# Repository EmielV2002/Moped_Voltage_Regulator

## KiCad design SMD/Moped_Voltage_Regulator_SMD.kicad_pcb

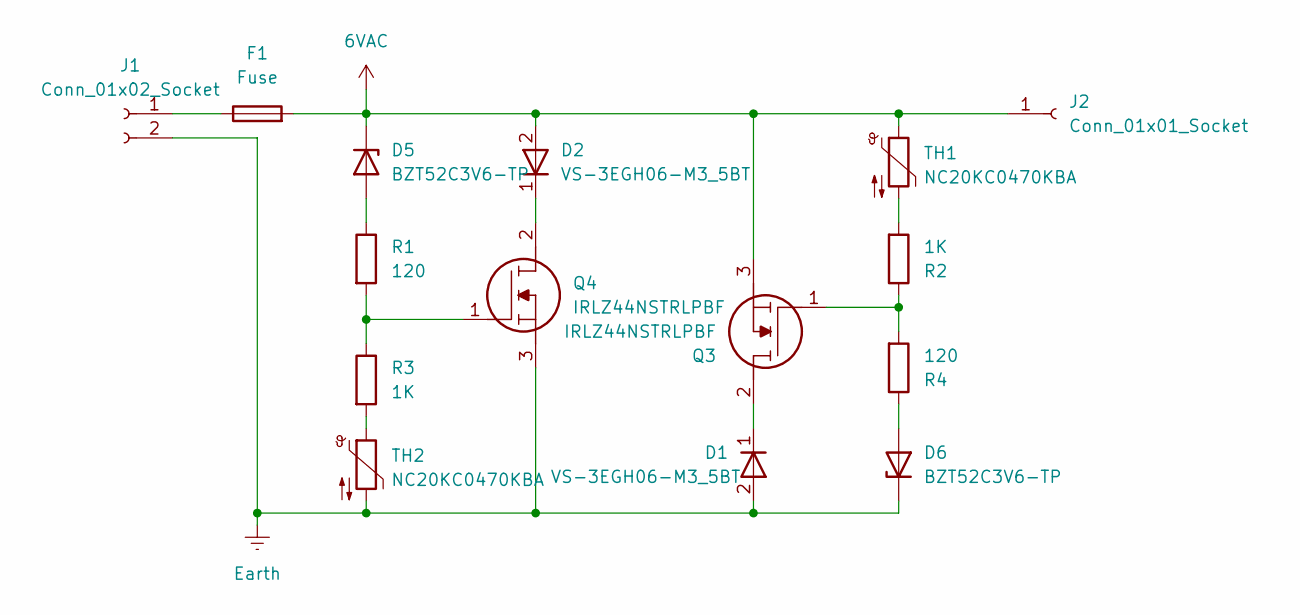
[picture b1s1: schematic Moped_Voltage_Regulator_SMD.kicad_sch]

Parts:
D1, D2: VS-3EGH06-M3_5BT; DIOM5436X244N; Manufacturer_Part_Number VS-3EGH06-M3/5BT; Mouser Part Number 78-VS-3EGH06-M3/5BT
D5, D6: BZT52C3V6-TP; D_SOD-123F
F1: Fuse; Fuseholder_Blade_Mini_Keystone_3568
J1: Conn_01x02_Socket; SolderWire-0.75sqmm_1x02_P4.8mm_D1.25mm_OD2.3mm
J2: Conn_01x01_Socket; SolderWire-0.75sqmm_1x01_D1.25mm_OD2.3mm
Q3, Q4: IRLZ44NSTRLPBF; IRF2804STRLPBF; Manufacturer_Part_Number IRLZ44NSTRLPBF; Mouser Part Number 942-IRLZ44NSTRLPBF
R1, R4: 120; R_1206_3216Metric
R2, R3: 1K; R_1206_3216Metric
TH1, TH2: NC20KC0470KBA; R_Axial_DIN0204_L3.6mm_D1.6mm_P1.90mm_Vertical

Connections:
6VAC: D2.2 (A), D5.1 (K), F1.2, J2.1, Q3.3, TH1.1
Earth: D1.2 (A), D6.1 (K), J1.2, Q4.3, TH2.2
unnamed: D1.1 (K), Q3.2
unnamed: D2.1 (K), Q4.2
unnamed: D5.2 (A), R1.1
unnamed: D6.2 (A), R4.1
unnamed: F1.1, J1.1
unnamed: Q3.1, R2.1, R4.2
unnamed: Q4.1, R1.2, R3.1
unnamed: R2.2, TH1.2
unnamed: R3.2, TH2.1

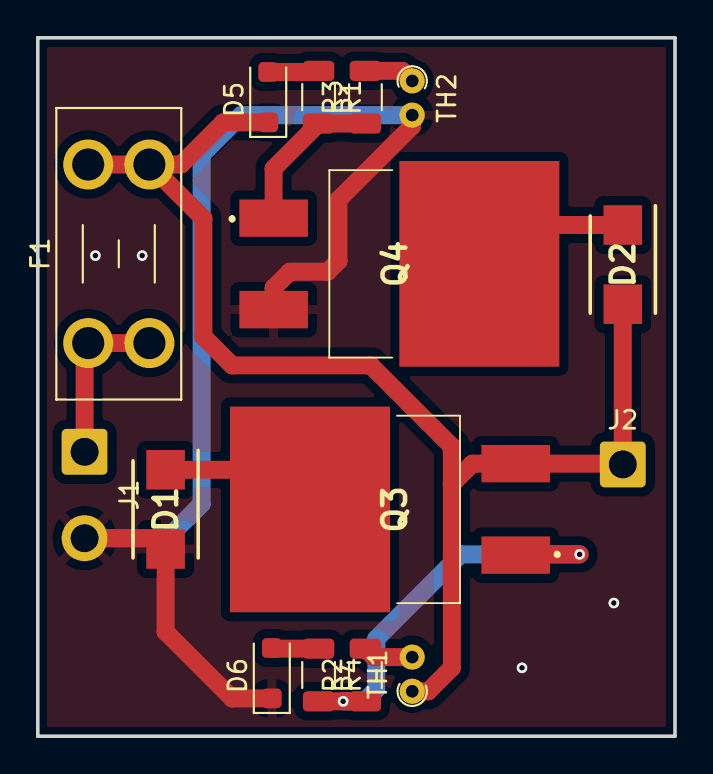
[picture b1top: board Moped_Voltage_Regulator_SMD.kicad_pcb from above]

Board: 2 copper layers, 35.4 x 38.8 mm, 15 parts (0 on the bottom side), 11 nets.

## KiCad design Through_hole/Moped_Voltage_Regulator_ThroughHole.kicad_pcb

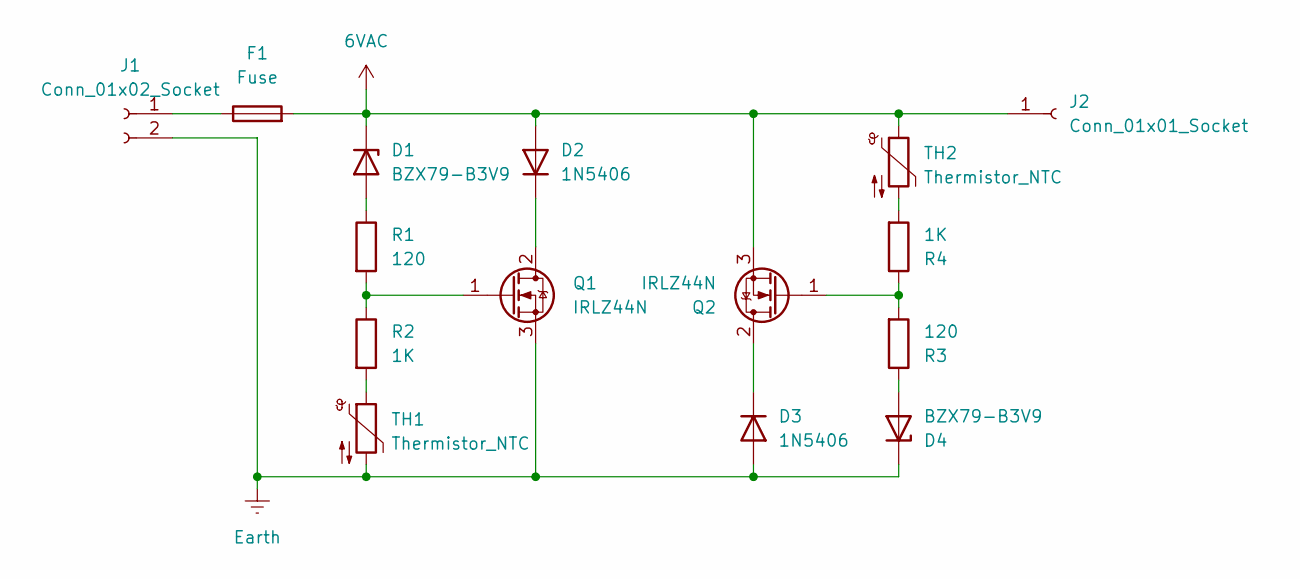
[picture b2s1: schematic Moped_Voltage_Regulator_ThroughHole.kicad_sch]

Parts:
D1, D4: BZX79-B3V9; D_DO-35_SOD27_P7.62mm_Horizontal
D2, D3: 1N5406; D_DO-201AD_P15.24mm_Horizontal
F1: Fuse; Fuseholder_Blade_Mini_Keystone_3568
J1: Conn_01x02_Socket; SolderWire-0.75sqmm_1x02_P4.8mm_D1.25mm_OD2.3mm
J2: Conn_01x01_Socket; SolderWire-0.75sqmm_1x01_D1.25mm_OD2.3mm
Q1, Q2: IRLZ44N; TO-220-3_Vertical
R1, R3: 120; R_Axial_DIN0204_L3.6mm_D1.6mm_P7.62mm_Horizontal
R2, R4: 1K; R_Axial_DIN0204_L3.6mm_D1.6mm_P7.62mm_Horizontal
TH1, TH2: Thermistor_NTC; R_Axial_DIN0204_L3.6mm_D1.6mm_P1.90mm_Vertical

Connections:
6VAC: D1.1 (K), D2.2 (A), F1.2, J2.1, Q2.3 (S), TH2.1
Earth: D3.2 (A), D4.1 (K), J1.2, Q1.3 (S), TH1.2
unnamed: D1.2 (A), R1.1
unnamed: D2.1 (K), Q1.2 (D)
unnamed: D3.1 (K), Q2.2 (D)
unnamed: D4.2 (A), R3.1
unnamed: F1.1, J1.1
unnamed: Q1.1 (G), R1.2, R2.1
unnamed: Q2.1 (G), R3.2, R4.1
unnamed: R2.2, TH1.1
unnamed: R4.2, TH2.2

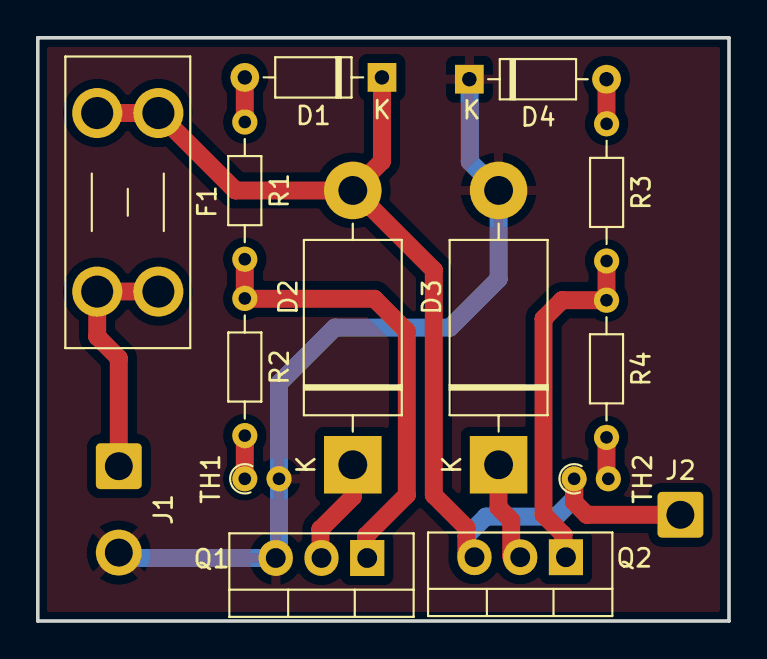
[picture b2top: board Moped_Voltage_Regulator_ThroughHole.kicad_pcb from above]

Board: 2 copper layers, 38.4 x 32.4 mm, 15 parts (0 on the bottom side), 11 nets.

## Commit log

2024-05-02 Create Moped_Voltage_Regulator
2024-05-03 Updated schematic and PCB
2024-05-03 Added SMD version
2024-05-05 Added simulations
2024-05-07 Updated PCB
